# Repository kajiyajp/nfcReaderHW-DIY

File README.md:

# NFC 読み取り機（XIAO RP2040 ＋ PN532 モジュール）

> 作成：2026-11-15 ／ 更新：2026-11-20（市販の XIAO RP2040 ＋ PN532 モジュールを基本とする方針に変更。自作基板は `archive/pcb/` に凍結）
> 目的：NTAG215 などの NFC カードをかざすと、番号を USB キーボードとして打ち込む読み取り機の資料

## 1. 何を作るか

- 社員証（NTAG215 シールなど ISO 14443A のカード）をかざすと、**UID（カードの番号）を 16 進で打ち込み、Enter を送る** USB キーボード型の読み取り機
- PC からは USB キーボードに見えるので、**ドライバも PC 側の設定も要らない**。MeetingLog の確認端末（`/kiosk`）にそのまま挿して使う
- 部品は市販品だけ（XIAO RP2040、PN532 NFC モジュール V3、ジャンパ線）。3D プリントのケースに入れる

### 非ゴール
- カードへの書き込み、NDEF（カードの中のデータ）の読み出し（UID だけを読む）
- Wi-Fi / BLE で送ること（必要になったら別に考える）

### 方針の変更（2026-11-20）
- PN532 ＋ ESP32-S3 の **自作基板（rev 0.2）は凍結** した。発注はしていない。資料と KiCad 一式は [archive/pcb/](archive/pcb/README.md) に、凍結した時点はタグ `pcb-rev0.2-frozen` に残している
- 理由：市販の部品の組み合わせで、実機で社員証を読めることを確かめられた（2026-11-19）。自作基板は、アンテナの調整（NanoVNA）と発注の手間・費用が大きい

## 2. 構成

```
PC ──USB-C── XIAO RP2040 ──I2C(SDA=D4, SCL=D5)── PN532 モジュール V3 ))) カード
             （USB キーボード ＋ シリアル）              （アンテナ・整合回路つき）
```

| 部品 | 例 | メモ |
|---|---|---|
| マイコン | Seeed XIAO RP2040 | USB キーボード（HID）になれる |
| NFC | PN532 NFC RFID モジュール V3（Amazon ASIN B0H6ZYCJVQ など） | 約 40×43mm。読み取り距離 4〜6cm。スイッチを I2C（SW1=ON、SW2=OFF）にする |
| ブザー（任意） | アクティブブザー（Amazon ASIN B0CZJ5DGDH）＋ 470Ω（直列） | 読めたら「ピッ」。D3 から鳴らす。配線は [firmware/README.md](firmware/README.md) |
| ケース | [case/](case/README.md) | 3D プリント（PLA / PETG） |

### 配線（4 本）

| PN532 モジュール | XIAO RP2040 |
|---|---|
| VCC | 3V3 |
| GND | GND |
| SDA | D4 |
| SCL | D5 |

IRQ・RSTO はつながなくてよい。5V から取るときの注意は [firmware/README.md](firmware/README.md) を読む。

## 3. 打ち込む文字

| 設定 | 例 |
|---|---|
| 場所の番号なし（最初の状態） | `04A1B2C3D4E5F6` ⏎ |
| 場所の番号 12（シリアルから `LOC 12`） | `L12U04A1B2C3D4E5F6` ⏎ |

- NTAG は 7 バイトで 14 桁、MIFARE Classic などは 4 バイトで 8 桁になる
- 0〜9・A〜F・L・U だけなので、キーボードの配列（日本語・英語）によらず同じ文字が入る
- **PC の IME（日本語入力）はオフにしておく。** オンだと全角で入り、Enter が変換の確定に使われる
- 同じカードは、1.5 秒以上離してからかざすと、もう一度送る（置いたままでは送り直さない）

## 4. 書き込みと動作確認

1. Arduino IDE に **Raspberry Pi Pico/RP2040/RP2350**（Earle F. Philhower 版）のボード定義と **Adafruit PN532** ライブラリを入れる
2. ボードを **Seeed XIAO RP2040** にして、[xiao_rp2040_pn532_hid.ino](firmware/xiao_rp2040_pn532_hid/xiao_rp2040_pn532_hid.ino) を書き込む（最初の 1 回は BOOT ボタンを押しながら USB を挿す）
3. 書き込んだあとは **USB を挿し直す**（PN532 が通信の途中で固まることがあるため）
4. メモ帳を開いてカードをかざし、番号と改行が入れば OK

LED の色と音（読めたら緑とピッ）、シリアル（115200bps）の表示の読み方、うまくいかないときの対処は [firmware/README.md](firmware/README.md) にある。

## 5. フォルダ

| 場所 | 内容 |
|---|---|
| `firmware/` | ファームウェア（Arduino C++）と、その使い方・確かめた内容・不具合の避け方 |
| `case/` | 3D プリントのケース（STEP / STL と、それを作る FreeCAD スクリプト） |
| `archive/pcb/` | **凍結**：自作基板（PN532 ＋ ESP32-S3、rev 0.2）の設計資料・KiCad 一式・入稿ファイル |
| `TODO.md` / `glossary.md` | 残作業 / 用語集 |

## 6. 注意

- 市販の PN532 モジュールには技適の表示がない。社内の常設機器として使うかは、市販のキーボード型の読み取り機と比べて決める
- UID はコピーできるカードもある。確認端末は「読んだことの記録」用として使う（MeetingLog の `docs/nfc-card.md`「安全について」）

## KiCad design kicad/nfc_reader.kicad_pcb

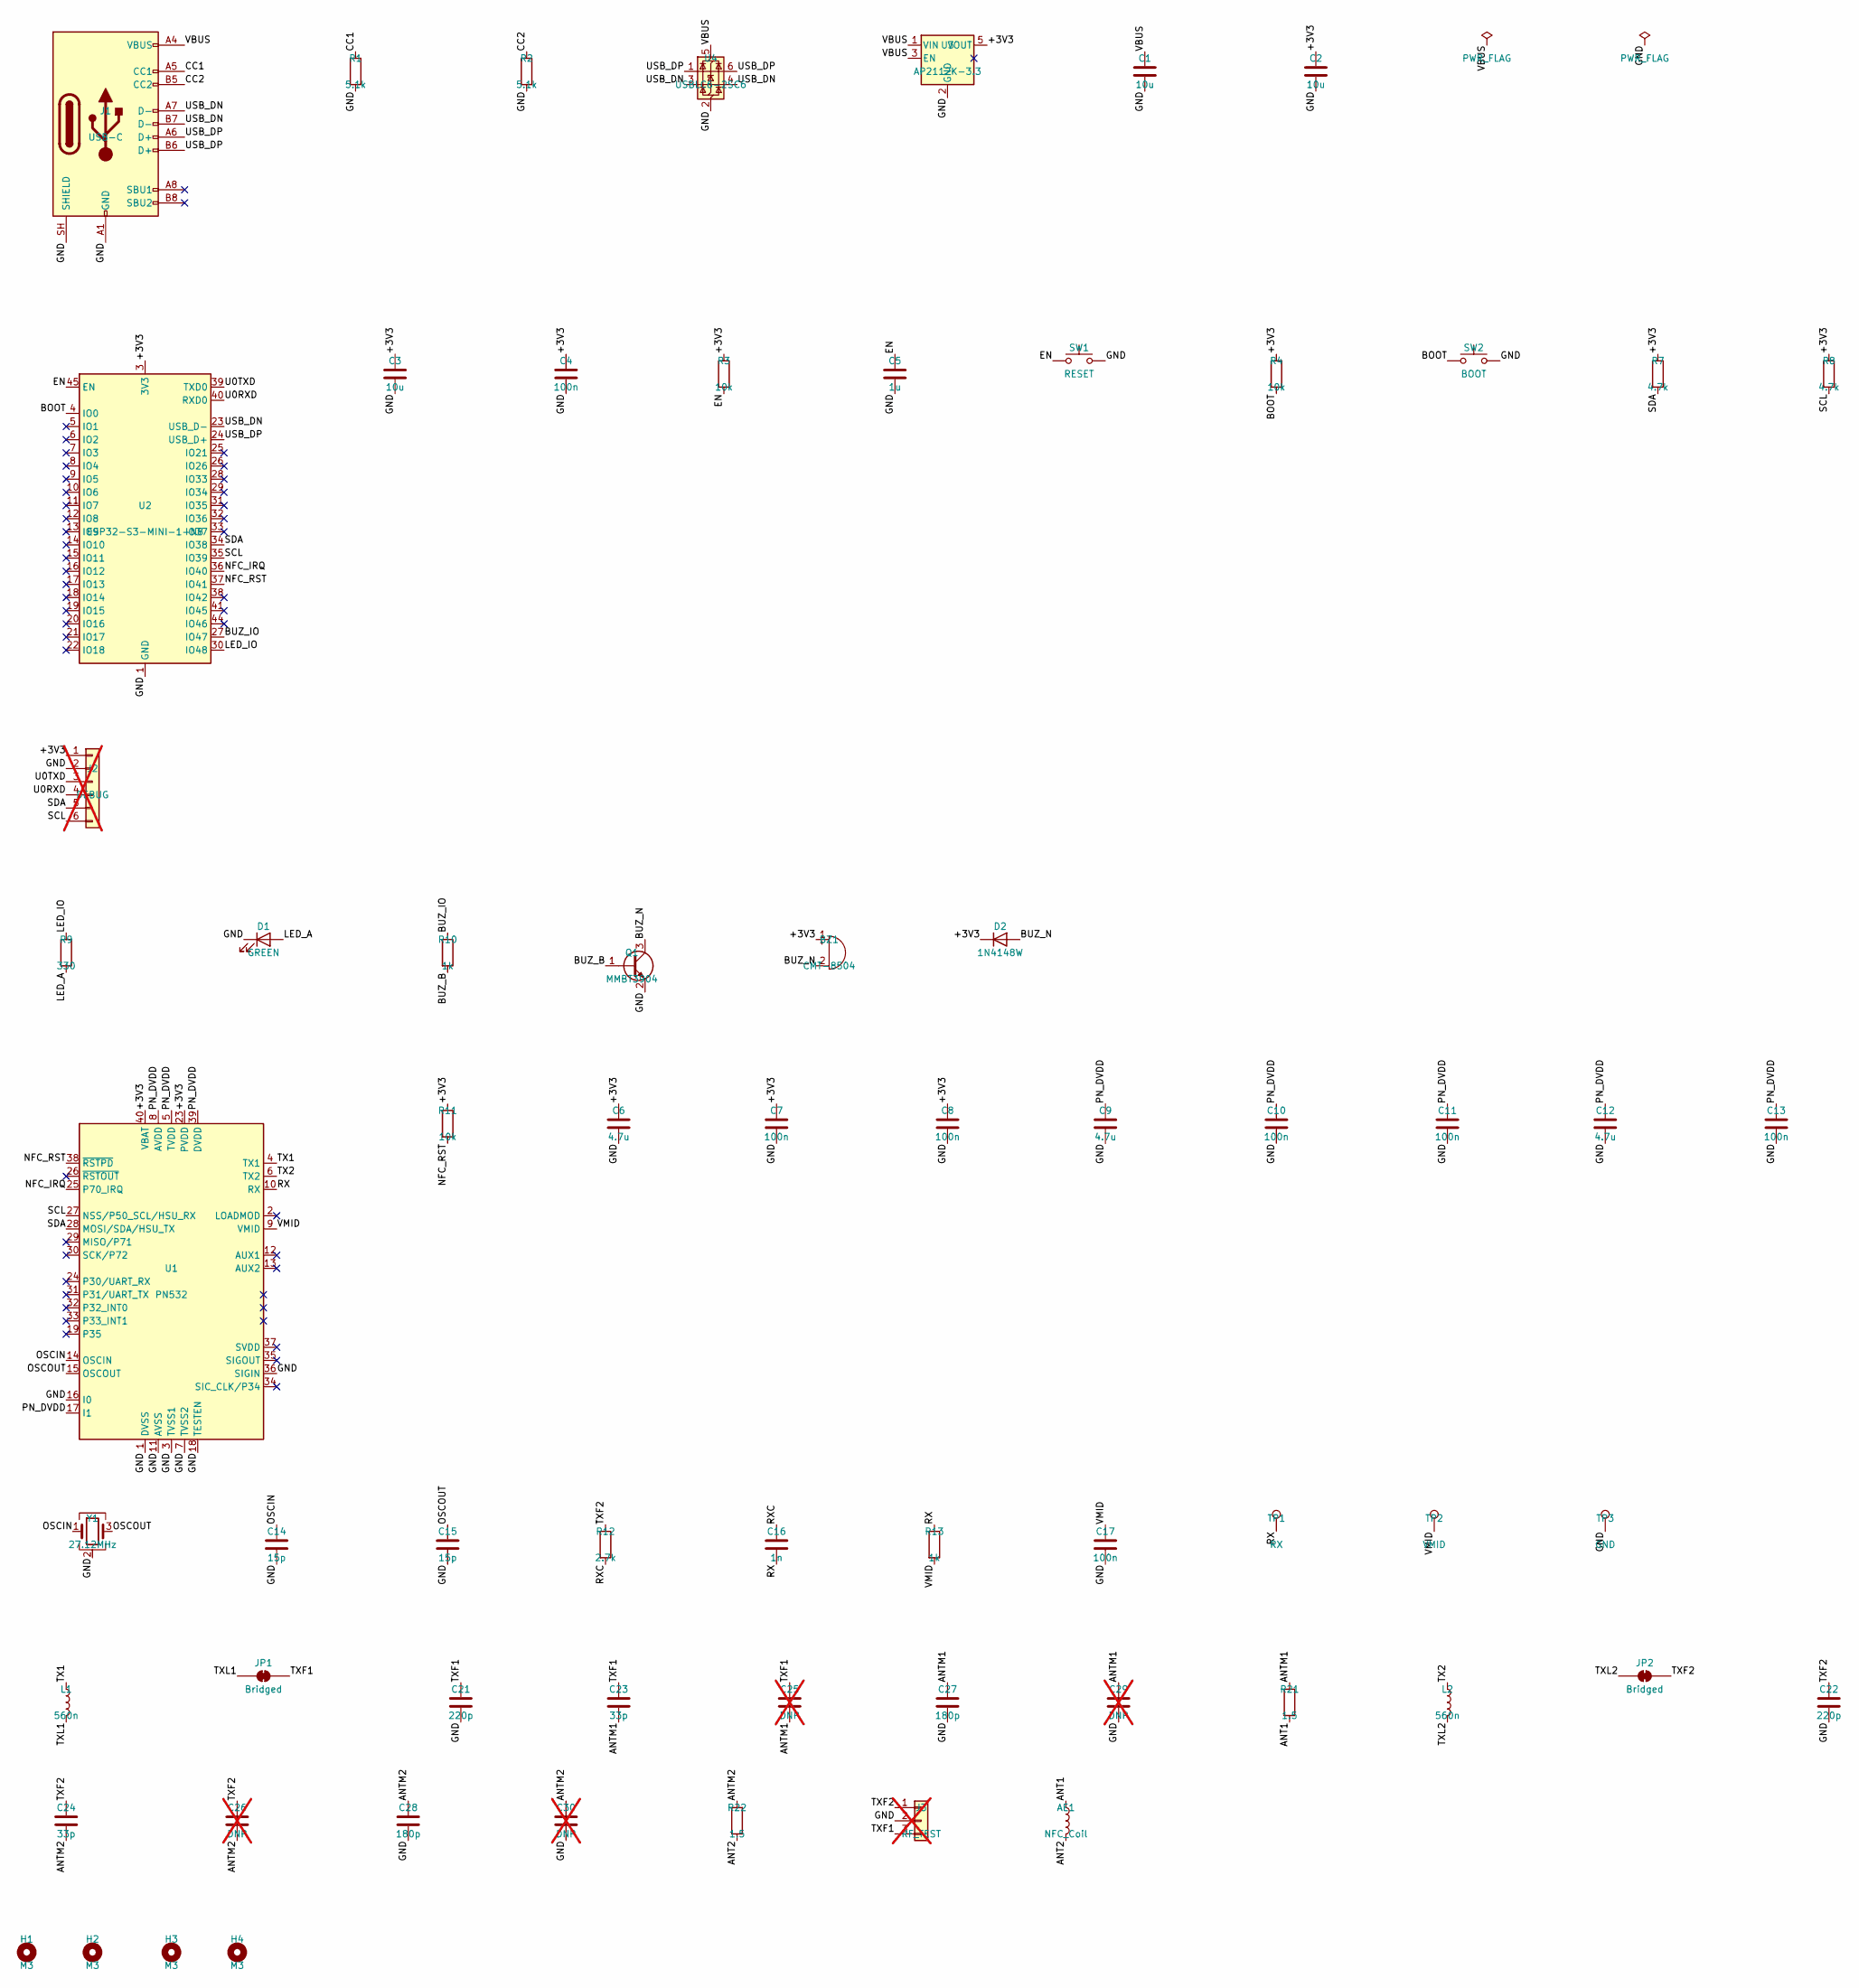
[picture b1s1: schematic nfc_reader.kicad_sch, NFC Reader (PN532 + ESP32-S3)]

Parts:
AE1: NFC_Coil; NFC_Coil_45x35_4T
BZ1: CMT-8504; MagneticBuzzer_CUI_CMT-8504-100-SMT; MPN CMT-8504-100-SMT-TR
C1, C2, C3: 10u; C_0805_2012Metric
C4, C7, C8, C10, C11, C13, C17: 100n; C_0402_1005Metric
C5: 1u; C_0402_1005Metric
C6, C9, C12: 4.7u; C_0603_1608Metric
C14, C15: 15p; C_0402_1005Metric
C16: 1n; C_0402_1005Metric
C21, C22: 220p; C_0603_1608Metric
C23, C24: 33p; C_0603_1608Metric
C25, C26, C29, C30: DNP; C_0603_1608Metric; not fitted
C27, C28: 180p; C_0603_1608Metric
D1: GREEN; LED_0603_1608Metric; MPN KT-0603G; LCSC C12624
D2: 1N4148W; D_SOD-123; MPN 1N4148W
H1, H2, H3, H4: M3; MountingHole_3.2mm_M3
J1: USB-C; USB_C_Receptacle_GCT_USB4105-xx-A_16P_TopMnt_Horizontal; MPN USB4105-GF-A
J2: DEBUG; PinHeader_1x06_P2.54mm_Vertical; not fitted
J3: RF_TEST; PinHeader_1x03_P2.54mm_Vertical; not fitted
JP1, JP2: Bridged; SolderJumper-2_P1.3mm_Bridged_RoundedPad1.0x1.5mm
L1, L2: 560n; L_0805_2012Metric; MPN FHW0805UFR56JST; LCSC C304279
Q1: MMBT3904; SOT-23; MPN MMBT3904
R1, R2: 5.1k; R_0402_1005Metric
R3, R4, R11: 10k; R_0402_1005Metric
R7, R8: 4.7k; R_0402_1005Metric
R9: 330; R_0402_1005Metric
R10, R13: 1k; R_0402_1005Metric
R12: 2.7k; R_0402_1005Metric
R21, R22: 1.5; R_0603_1608Metric
SW1: RESET; SW_SPST_TL3342; MPN TL3342F160QG/TR; LCSC C2918453
SW2: BOOT; SW_SPST_TL3342; MPN TL3342F160QG/TR; LCSC C2918453
TP1: RX; TestPoint_Pad_1.0x1.0mm
TP2: VMID; TestPoint_Pad_1.0x1.0mm
TP3: GND; TestPoint_Pad_1.0x1.0mm
U1: PN532; HVQFN-40-1EP_6x6mm_P0.5mm_EP4.1x4.1mm; MPN PN5321A3HN/C106; LCSC C880904
U2: ESP32-S3-MINI-1-N8; ESP32-S2-MINI-1; MPN ESP32-S3-MINI-1-N8; LCSC C2913206
U3: AP2112K-3.3; SOT-23-5; MPN AP2112K-3.3TRG1
U4: USBLC6-2SC6; SOT-23-6; MPN USBLC6-2SC6
Y1: 27.12MHz; Crystal_SMD_3225-4Pin_3.2x2.5mm; MPN S3B27.120000F1010F30; LCSC C439059

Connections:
/+3V3: BZ1.1 (+), C2.1, C3.1, C4.1, C6.1, C7.1, C8.1, D2.1 (K), J2.1, R3.1, R4.1, R7.1, R8.1, R11.1, U1.23 (PVDD), U1.40 (VBAT), U2.3 (3V3), U3.5 (VOUT)
/ANT1: AE1.1, R21.2
/ANT2: AE1.2, R22.2
/ANTM1: C23.2, C25.2, C27.1, C29.1, R21.1
/ANTM2: C24.2, C26.2, C28.1, C30.1, R22.1
/BOOT: R4.2, SW2.1, U2.4 (IO0)
/BUZ_B: Q1.1 (B), R10.2
/BUZ_IO: R10.1, U2.27 (IO47)
/BUZ_N: BZ1.2 (-), D2.2 (A), Q1.3 (C)
/CC1: J1.A5 (CC1), R1.1
/CC2: J1.B5 (CC2), R2.1
/EN: C5.1, R3.2, SW1.1, U2.45 (EN)
/GND: C1.2, C2.2, C3.2, C4.2, C5.2, C6.2, C7.2, C8.2, C9.2, C10.2, C11.2, C12.2, C13.2, C14.2, C15.2, C17.2, C21.2, C22.2, C27.2, C28.2, C29.2, C30.2, D1.1 (K), J1.A1 (GND), J1.A12 (GND), J1.B1 (GND), J1.B12 (GND), J1.SH (SHIELD), J2.2, J3.2, Q1.2 (E), R1.2, R2.2, SW1.2, SW2.2, TP3.1, U1.1 (DVSS), U1.3 (TVSS1), U1.7 (TVSS2), U1.11 (AVSS), U1.16 (I0), U1.18 (TESTEN), U1.36 (SIGIN), U1.41 (AVSS), U2.1 (GND), U2.2 (GND), U2.42 (GND), U2.43 (GND), U2.46 (GND), U2.47 (GND), U2.48 (GND), U2.49 (GND), U2.50 (GND), U2.51 (GND), U2.52 (GND), U2.53 (GND), U2.54 (GND), U2.55 (GND), U2.56 (GND), U2.57 (GND), U2.58 (GND), U2.59 (GND), U2.60 (GND), U2.61 (GND), U2.62 (GND), U2.63 (GND), U2.64 (GND), U2.65 (GND), U3.2 (GND), U4.2 (GND), Y1.2 (G), Y1.4 (G)
/LED_A: D1.2 (A), R9.2
/LED_IO: R9.1, U2.30 (IO48)
/NFC_IRQ: U1.25 (P70_IRQ), U2.36 (IO40)
/NFC_RST: R11.2, U1.38 (~RSTPD), U2.37 (IO41)
/OSCIN: C14.1, U1.14 (OSCIN), Y1.1
/OSCOUT: C15.1, U1.15 (OSCOUT), Y1.3
/PN_DVDD: C9.1, C10.1, C11.1, C12.1, C13.1, U1.5 (TVDD), U1.8 (AVDD), U1.17 (I1), U1.39 (DVDD)
/RX: C16.2, R13.1, TP1.1, U1.10 (RX)
/RXC: C16.1, R12.2
/SCL: J2.6, R8.2, U1.27 (NSS/P50_SCL/HSU_RX), U2.35 (IO39)
/SDA: J2.5, R7.2, U1.28 (MOSI/SDA/HSU_TX), U2.34 (IO38)
/TX1: L1.1, U1.4 (TX1)
/TX2: L2.1, U1.6 (TX2)
/TXF1: C21.1, C23.1, C25.1, J3.3, JP1.2 (B)
/TXF2: C22.1, C24.1, C26.1, J3.1, JP2.2 (B), R12.1
/TXL1: JP1.1 (A), L1.2
/TXL2: JP2.1 (A), L2.2
/U0RXD: J2.4, U2.40 (RXD0)
/U0TXD: J2.3, U2.39 (TXD0)
/USB_DN: J1.A7 (D-), J1.B7 (D-), U2.23 (USB_D-), U4.3 (I/O2), U4.4 (I/O2)
/USB_DP: J1.A6 (D+), J1.B6 (D+), U2.24 (USB_D+), U4.1 (I/O1), U4.6 (I/O1)
/VBUS: C1.1, J1.A4 (VBUS), J1.A9 (VBUS), J1.B4 (VBUS), J1.B9 (VBUS), U3.1 (VIN), U3.3 (EN), U4.5 (VBUS)
/VMID: C17.1, R13.2, TP2.1, U1.9 (VMID)

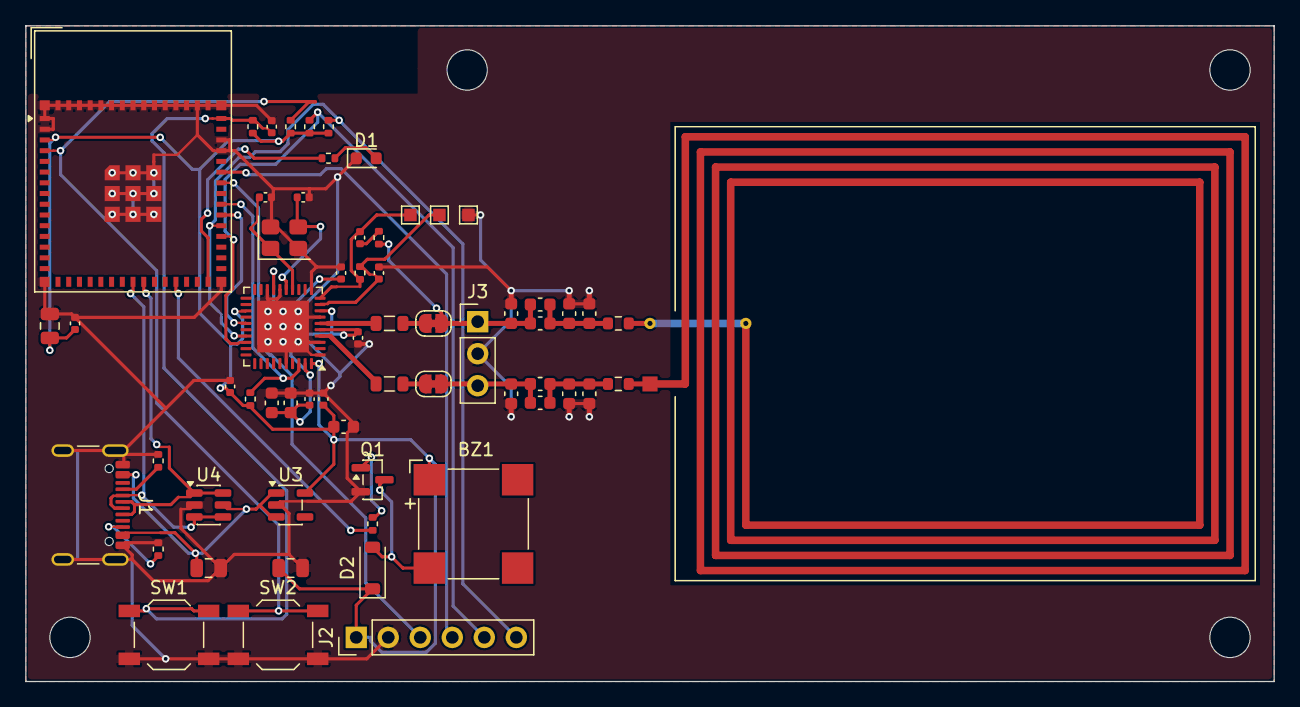
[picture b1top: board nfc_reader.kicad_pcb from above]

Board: 2 copper layers, 99.0 x 52.0 mm, 66 parts (0 on the bottom side), 36 nets.

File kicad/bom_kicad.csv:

"Designator","Value","Footprint","MPN","LCSC","Qty"
"AE1","NFC_Coil","nfc_reader:NFC_Coil_45x35_4T","","","1"
"BZ1","CMT-8504","Buzzer_Beeper:MagneticBuzzer_CUI_CMT-8504-100-SMT","CMT-8504-100-SMT-TR","","1"
"C1","10u","Capacitor_SMD:C_0805_2012Metric","","","1"
"C2","10u","Capacitor_SMD:C_0805_2012Metric","","","1"
"C3","10u","Capacitor_SMD:C_0805_2012Metric","","","1"
"C4","100n","Capacitor_SMD:C_0402_1005Metric","","","1"
"C5","1u","Capacitor_SMD:C_0402_1005Metric","","","1"
"C6","4.7u","Capacitor_SMD:C_0603_1608Metric","","","1"
"C7","100n","Capacitor_SMD:C_0402_1005Metric","","","1"
"C8","100n","Capacitor_SMD:C_0402_1005Metric","","","1"
"C9","4.7u","Capacitor_SMD:C_0603_1608Metric","","","1"
"C10","100n","Capacitor_SMD:C_0402_1005Metric","","","1"
"C11","100n","Capacitor_SMD:C_0402_1005Metric","","","1"
"C12","4.7u","Capacitor_SMD:C_0603_1608Metric","","","1"
"C13","100n","Capacitor_SMD:C_0402_1005Metric","","","1"
"C14","15p","Capacitor_SMD:C_0402_1005Metric","","","1"
"C15","15p","Capacitor_SMD:C_0402_1005Metric","","","1"
"C16","1n","Capacitor_SMD:C_0402_1005Metric","","","1"
"C17","100n","Capacitor_SMD:C_0402_1005Metric","","","1"
"C21","220p","Capacitor_SMD:C_0603_1608Metric","","","1"
"C22","220p","Capacitor_SMD:C_0603_1608Metric","","","1"
"C23","33p","Capacitor_SMD:C_0603_1608Metric","","","1"
"C24","33p","Capacitor_SMD:C_0603_1608Metric","","","1"
"C27","180p","Capacitor_SMD:C_0603_1608Metric","","","1"
"C28","180p","Capacitor_SMD:C_0603_1608Metric","","","1"
"D1","GREEN","LED_SMD:LED_0603_1608Metric","KT-0603G","C12624","1"
"D2","1N4148W","Diode_SMD:D_SOD-123","1N4148W","","1"
"H1","M3","MountingHole:MountingHole_3.2mm_M3","","","1"
"H2","M3","MountingHole:MountingHole_3.2mm_M3","","","1"
"H3","M3","MountingHole:MountingHole_3.2mm_M3","","","1"
"H4","M3","MountingHole:MountingHole_3.2mm_M3","","","1"
"J1","USB-C","Connector_USB:USB_C_Receptacle_GCT_USB4105-xx-A_16P_TopMnt_Horizontal","USB4105-GF-A","","1"
"L1","560n","Inductor_SMD:L_0805_2012Metric","FHW0805UFR56JST","C304279","1"
"L2","560n","Inductor_SMD:L_0805_2012Metric","FHW0805UFR56JST","C304279","1"
"Q1","MMBT3904","Package_TO_SOT_SMD:SOT-23","MMBT3904","","1"
"R1","5.1k","Resistor_SMD:R_0402_1005Metric","","","1"
"R2","5.1k","Resistor_SMD:R_0402_1005Metric","","","1"
"R3","10k","Resistor_SMD:R_0402_1005Metric","","","1"
"R4","10k","Resistor_SMD:R_0402_1005Metric","","","1"
"R7","4.7k","Resistor_SMD:R_0402_1005Metric","","","1"
"R8","4.7k","Resistor_SMD:R_0402_1005Metric","","","1"
"R9","330","Resistor_SMD:R_0402_1005Metric","","","1"
"R10","1k","Resistor_SMD:R_0402_1005Metric","","","1"
"R11","10k","Resistor_SMD:R_0402_1005Metric","","","1"
"R12","2.7k","Resistor_SMD:R_0402_1005Metric","","","1"
"R13","1k","Resistor_SMD:R_0402_1005Metric","","","1"
"R21","1.5","Resistor_SMD:R_0603_1608Metric","","","1"
"R22","1.5","Resistor_SMD:R_0603_1608Metric","","","1"
"SW1","RESET","Button_Switch_SMD:SW_SPST_TL3342","TL3342F160QG/TR","C2918453","1"
"SW2","BOOT","Button_Switch_SMD:SW_SPST_TL3342","TL3342F160QG/TR","C2918453","1"
"TP1","RX","TestPoint:TestPoint_Pad_1.0x1.0mm","","","1"
"TP2","VMID","TestPoint:TestPoint_Pad_1.0x1.0mm","","","1"
"TP3","GND","TestPoint:TestPoint_Pad_1.0x1.0mm","","","1"
"U1","PN532","Package_DFN_QFN:HVQFN-40-1EP_6x6mm_P0.5mm_EP4.1x4.1mm","PN5321A3HN/C106","C880904","1"
"U2","ESP32-S3-MINI-1-N8","RF_Module:ESP32-S2-MINI-1","ESP32-S3-MINI-1-N8","C2913206","1"
"U3","AP2112K-3.3","Package_TO_SOT_SMD:SOT-23-5","AP2112K-3.3TRG1","","1"
"U4","USBLC6-2SC6","Package_TO_SOT_SMD:SOT-23-6","USBLC6-2SC6","","1"
"Y1","27.12MHz","Crystal:Crystal_SMD_3225-4Pin_3.2x2.5mm","S3B27.120000F1010F30","C439059","1"

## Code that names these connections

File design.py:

# 作成日: 2026-11-15 ／ 更新: 2026-11-16（MCU を ESP32-S3-MINI-1 に変更、テストポイント・デバッグヘッダ追加、型番決定、
#   RF 測定用のはんだジャンパ JP1/JP2 と測定端子 J3 を追加）
# 目的: NFCリーダー基板の部品と接続（ネット）の唯一の定義。回路図・基板生成スクリプトはここを読む

from dataclasses import dataclass


@dataclass
class Part:
    ref: str
    lib: str              # "ライブラリ:シンボル名"
    value: str
    footprint: str
    nets: dict            # ピン番号 -> ネット名（書かないピンは未接続扱い）
    mpn: str = ""
    dnp: bool = False     # True = 未実装（予備パッド）
    group: str = ""       # 回路図の配置グループ
    note: str = ""
    lcsc: str = ""        # LCSC / JLC の部品番号（Fusion 見積もり時の参考。在庫は発注時に再確認）


R0402 = "Resistor_SMD:R_0402_1005Metric"
R0603 = "Resistor_SMD:R_0603_1608Metric"
C0402 = "Capacitor_SMD:C_0402_1005Metric"
C0603 = "Capacitor_SMD:C_0603_1608Metric"
C0805 = "Capacitor_SMD:C_0805_2012Metric"
TP_FP = "TestPoint:TestPoint_Pad_1.0x1.0mm"
ANT_FP = "nfc_reader:NFC_Coil_45x35_4T"   # 自作フットプリント（gen_coil.py で生成）

PARTS = []


# 部品を追加するヘルパー
def add(*a, **k):
    PARTS.append(Part(*a, **k))


# 2端子部品（R/C/L）を追加するヘルパー
def two(ref, kind, value, fp, n1, n2, group, mpn="", dnp=False, note="", lcsc=""):
    add(ref, f"Device:{kind}", value, fp, {"1": n1, "2": n2}, mpn=mpn, dnp=dnp, group=group, note=note, lcsc=lcsc)


# ===== USB / 電源 =====
add("J1", "Connector:USB_C_Receptacle_USB2.0_16P", "USB-C",
    "Connector_USB:USB_C_Receptacle_GCT_USB4105-xx-A_16P_TopMnt_Horizontal",
    {"A1": "GND", "A12": "GND", "B1": "GND", "B12": "GND", "SH": "GND",
     "A4": "VBUS", "A9": "VBUS", "B4": "VBUS", "B9": "VBUS",
     "A5": "CC1", "B5": "CC2", "A6": "USB_DP", "B6": "USB_DP", "A7": "USB_DN", "B7": "USB_DN"},
    mpn="USB4105-GF-A", group="power")
two("R1", "R", "5.1k", R0402, "CC1", "GND", "power")
two("R2", "R", "5.1k", R0402, "CC2", "GND", "power")
add("U4", "Power_Protection:USBLC6-2SC6", "USBLC6-2SC6", "Package_TO_SOT_SMD:SOT-23-6",
    {"1": "USB_DP", "6": "USB_DP", "3": "USB_DN", "4": "USB_DN", "5": "VBUS", "2": "GND"},
    mpn="USBLC6-2SC6", group="power")
add("U3", "Regulator_Linear:AP2112K-3.3", "AP2112K-3.3", "Package_TO_SOT_SMD:SOT-23-5",
    {"1": "VBUS", "3": "VBUS", "2": "GND", "5": "+3V3"}, mpn="AP2112K-3.3TRG1", group="power")
two("C1", "C", "10u", C0805, "VBUS", "GND", "power")
two("C2", "C", "10u", C0805, "+3V3", "GND", "power")
add("#FLG1", "power:PWR_FLAG", "PWR_FLAG", "", {"1": "VBUS"}, group="power")
add("#FLG2", "power:PWR_FLAG", "PWR_FLAG", "", {"1": "GND"}, group="power")

# ===== ESP32-S3 =====
# ESP32-S3-MINI-1-N8（フラッシュ8MB・PSRAMなし）。KiCad標準シンボルのフットプリントは S2-MINI-1（同じ外形・ピン配置）
# USB は GPIO19/20（ピン23/24）。ファームウェアで USB Serial/JTAG（書き込み）と USB OTG（HIDキーボード）を切り替えられる
# ストラップピン GPIO3・45・46 は未接続（内部プルのまま）。GPIO26・33〜37 は PSRAM 付き品と兼用しないよう使わない
add("U2", "RF_Module:ESP32-S3-MINI-1", "ESP32-S3-MINI-1-N8", "RF_Module:ESP32-S2-MINI-1",
    {"3": "+3V3", "45": "EN", "4": "BOOT",
     "1": "GND", "2": "GND", "42": "GND", "43": "GND",
     **{str(n): "GND" for n in range(46, 66)},
     "34": "SDA", "35": "SCL", "36": "NFC_IRQ", "37": "NFC_RST",     # GPIO38/39/40/41（PN532 側の辺）
     "30": "LED_IO", "27": "BUZ_IO",                                  # GPIO48 / GPIO47
     "39": "U0TXD", "40": "U0RXD",                                    # デバッグ用 UART0
     "23": "USB_DN", "24": "USB_DP"},
    mpn="ESP32-S3-MINI-1-N8", lcsc="C2913206", group="mcu")
two("C3", "C", "10u", C0805, "+3V3", "GND", "mcu")
two("C4", "C", "100n", C0402, "+3V3", "GND", "mcu")
two("R3", "R", "10k", R0402, "+3V3", "EN", "mcu")
two("C5", "C", "1u", C0402, "EN", "GND", "mcu")
add("SW1", "Switch:SW_Push", "RESET", "Button_Switch_SMD:SW_SPST_TL3342", {"1": "EN", "2": "GND"},
    mpn="TL3342F160QG/TR", lcsc="C2918453", group="mcu")
two("R4", "R", "10k", R0402, "+3V3", "BOOT", "mcu", note="GPIO0 ストラップ: 起動時High")
add("SW2", "Switch:SW_Push", "BOOT", "Button_Switch_SMD:SW_SPST_TL3342", {"1": "BOOT", "2": "GND"},
    mpn="TL3342F160QG/TR", lcsc="C2918453", group="mcu")
two("R7", "R", "4.7k", R0402, "+3V3", "SDA", "mcu")
two("R8", "R", "4.7k", R0402, "+3V3", "SCL", "mcu")
# デバッグ用ヘッダ（未実装。必要なときに手はんだ）: 3V3 / GND / TXD0 / RXD0 / SDA / SCL
add("J2", "Connector_Generic:Conn_01x06", "DEBUG", "Connector_PinHeader_2.54mm:PinHeader_1x06_P2.54mm_Vertical",
    {"1": "+3V3", "2": "GND", "3": "U0TXD", "4": "U0RXD", "5": "SDA", "6": "SCL"},
    dnp=True, group="mcu", note="UART0 / I2C")

# ===== UI（LED・ブザー） =====
two("R9", "R", "330", R0402, "LED_IO", "LED_A", "ui")
add("D1", "Device:LED", "GREEN", "LED_SMD:LED_0603_1608Metric", {"2": "LED_A", "1": "GND"},
    mpn="KT-0603G", lcsc="C12624", group="ui")
two("R10", "R", "1k", R0402, "BUZ_IO", "BUZ_B", "ui")
add("Q1", "Transistor_BJT:MMBT3904", "MMBT3904", "Package_TO_SOT_SMD:SOT-23",
    {"1": "BUZ_B", "2": "GND", "3": "BUZ_N"}, mpn="MMBT3904", group="ui")
add("BZ1", "Device:Buzzer", "CMT-8504", "Buzzer_Beeper:MagneticBuzzer_CUI_CMT-8504-100-SMT",
    {"1": "+3V3", "2": "BUZ_N"}, mpn="CMT-8504-100-SMT-TR", group="ui")
add("D2", "Device:D", "1N4148W", "Diode_SMD:D_SOD-123", {"1": "+3V3", "2": "BUZ_N"}, mpn="1N4148W", group="ui")

# ===== PN532 =====
# 供給状況: NXP は PN5321A3HN を「新規設計非推奨（NRND）」としている（後継は PN7160）。README §9 参照
add("U1", "RF_NFC:PN5321A3HN_C1xx", "PN532", "Package_DFN_QFN:HVQFN-40-1EP_6x6mm_P0.5mm_EP4.1x4.1mm",
    {"40": "+3V3", "23": "+3V3", "39": "PN_DVDD", "8": "PN_DVDD", "5": "PN_DVDD",
     "1": "GND", "3": "GND", "7": "GND", "11": "GND", "41": "GND",
     "16": "GND", "17": "PN_DVDD", "18": "GND", "36": "GND",          # I0=L, I1=H → I2C
     "27": "SCL", "28": "SDA", "25": "NFC_IRQ", "38": "NFC_RST",
     "14": "OSCIN", "15": "OSCOUT", "4": "TX1", "6": "TX2", "9": "VMID", "10": "RX"},
    mpn="PN5321A3HN/C106", lcsc="C880904", group="nfc")
two("R11", "R", "10k", R0402, "+3V3", "NFC_RST", "nfc")
two("C6", "C", "4.7u", C0603, "+3V3", "GND", "nfc", note="VBAT")
two("C7", "C", "100n", C0402, "+3V3", "GND", "nfc", note="VBAT")
two("C8", "C", "100n", C0402, "+3V3", "GND", "nfc", note="PVDD")
two("C9", "C", "4.7u", C0603, "PN_DVDD", "GND", "nfc", note="DVDD")
two("C10", "C", "100n", C0402, "PN_DVDD", "GND", "nfc", note="DVDD")
two("C11", "C", "100n", C0402, "PN_DVDD", "GND", "nfc", note="AVDD")
two("C12", "C", "4.7u", C0603, "PN_DVDD", "GND", "nfc", note="TVDD（大容量側。DVDD と同じネット）")
two("C13", "C", "100n", C0402, "PN_DVDD", "GND", "nfc", note="TVDD（TVDDピンの直近、整合部の2列の間）")
add("Y1", "Device:Crystal_GND24", "27.12MHz", "Crystal:Crystal_SMD_3225-4Pin_3.2x2.5mm",
    {"1": "OSCIN", "3": "OSCOUT", "2": "GND", "4": "GND"},
    mpn="S3B27.120000F1010F30", lcsc="C439059", group="nfc", note="CL=10pF（発注前にデータシートでCLを再確認）")
two("C14", "C", "15p", C0402, "OSCIN", "GND", "nfc", note="C0G")
two("C15", "C", "15p", C0402, "OSCOUT", "GND", "nfc", note="C0G")
# RX経路（データシート Fig.51）。PN532 の RX/VMID ピンに近い TX2 側のフィルタ出力から取る
two("R12", "R", "2.7k", R0402, "TXF2", "RXC", "nfc")
two("C16", "C", "1n", C0402, "RXC", "RX", "nfc")
two("R13", "R", "1k", R0402, "RX", "VMID", "nfc")
two("C17", "C", "100n", C0402, "VMID", "GND", "nfc")
# 調整・測定用テストポイント（TX/TXF は L1/L2 のパッドで測れるので置かない）
add("TP1", "Connector:TestPoint", "RX", TP_FP, {"1": "RX"}, group="nfc")
add("TP2", "Connector:TestPoint", "VMID", TP_FP, {"1": "VMID"}, group="nfc")
add("TP3", "Connector:TestPoint", "GND", TP_FP, {"1": "GND"}, group="nfc")

# ===== アンテナ整合（左右対称。C25〜C30 は予備パッド=未実装） =====
for side, tx in (("1", "TX1"), ("2", "TX2")):
    s = int(side)
    two(f"L{s}", "L", "560n", "Inductor_SMD:L_0805_2012Metric", tx, f"TXL{side}", "rf",
        mpn="FHW0805UFR56JST", lcsc="C304279", note="EMC L0（巻線 500mA。積層フェライトの150mA品は避ける）")
    # 測定用の切り離し（普段は銅箔でつながっている。NanoVNA で測るときはカッターで切り、終わったらはんだで戻す）
    add(f"JP{s}", "Jumper:SolderJumper_2_Bridged", "Bridged", "Jumper:SolderJumper-2_P1.3mm_Bridged_RoundedPad1.0x1.5mm",
        {"1": f"TXL{side}", "2": f"TXF{side}"}, group="rf", note="はんだジャンパ（部品なし）。RF 調整時に切る")
    two(f"C{20+s}", "C", "220p", C0603, f"TXF{side}", "GND", "rf", note="EMC C0 (C0G)")
    two(f"C{22+s}", "C", "33p", C0603, f"TXF{side}", f"ANTM{side}", "rf", note="整合 直列C1 (C0G)")
    two(f"C{24+s}", "C", "DNP", C0603, f"TXF{side}", f"ANTM{side}", "rf", dnp=True, note="C1 調整用予備")
    two(f"C{26+s}", "C", "180p", C0603, f"ANTM{side}", "GND", "rf", note="整合 並列C2 (C0G)")
    two(f"C{28+s}", "C", "DNP", C0603, f"ANTM{side}", "GND", "rf", dnp=True, note="C2 調整用予備")
    two(f"R{20+s}", "R", "1.5", R0603, f"ANTM{side}", f"ANT{side}", "rf", note="ダンピング Rq")
# NanoVNA 接続用（未実装。調整時だけピンヘッダを挿す）。TXF2 / GND / TXF1 を整合部の2列に重ねて並べる
add("J3", "Connector_Generic:Conn_01x03", "RF_TEST", "Connector_PinHeader_2.54mm:PinHeader_1x03_P2.54mm_Vertical",
    {"1": "TXF2", "2": "GND", "3": "TXF1"}, dnp=True, group="rf", note="JP1/JP2 を切って、1:1 バラン経由で 1-3 間を差動で測る")
add("AE1", "Device:L", "NFC_Coil", ANT_FP, {"1": "ANT1", "2": "ANT2"}, group="rf", note="基板パターン 約1.34uH")

# ===== 取付穴 =====
for i in range(1, 5):
    add(f"H{i}", "Mechanical:MountingHole", "M3", "MountingHole:MountingHole_3.2mm_M3", {}, group="mech")
